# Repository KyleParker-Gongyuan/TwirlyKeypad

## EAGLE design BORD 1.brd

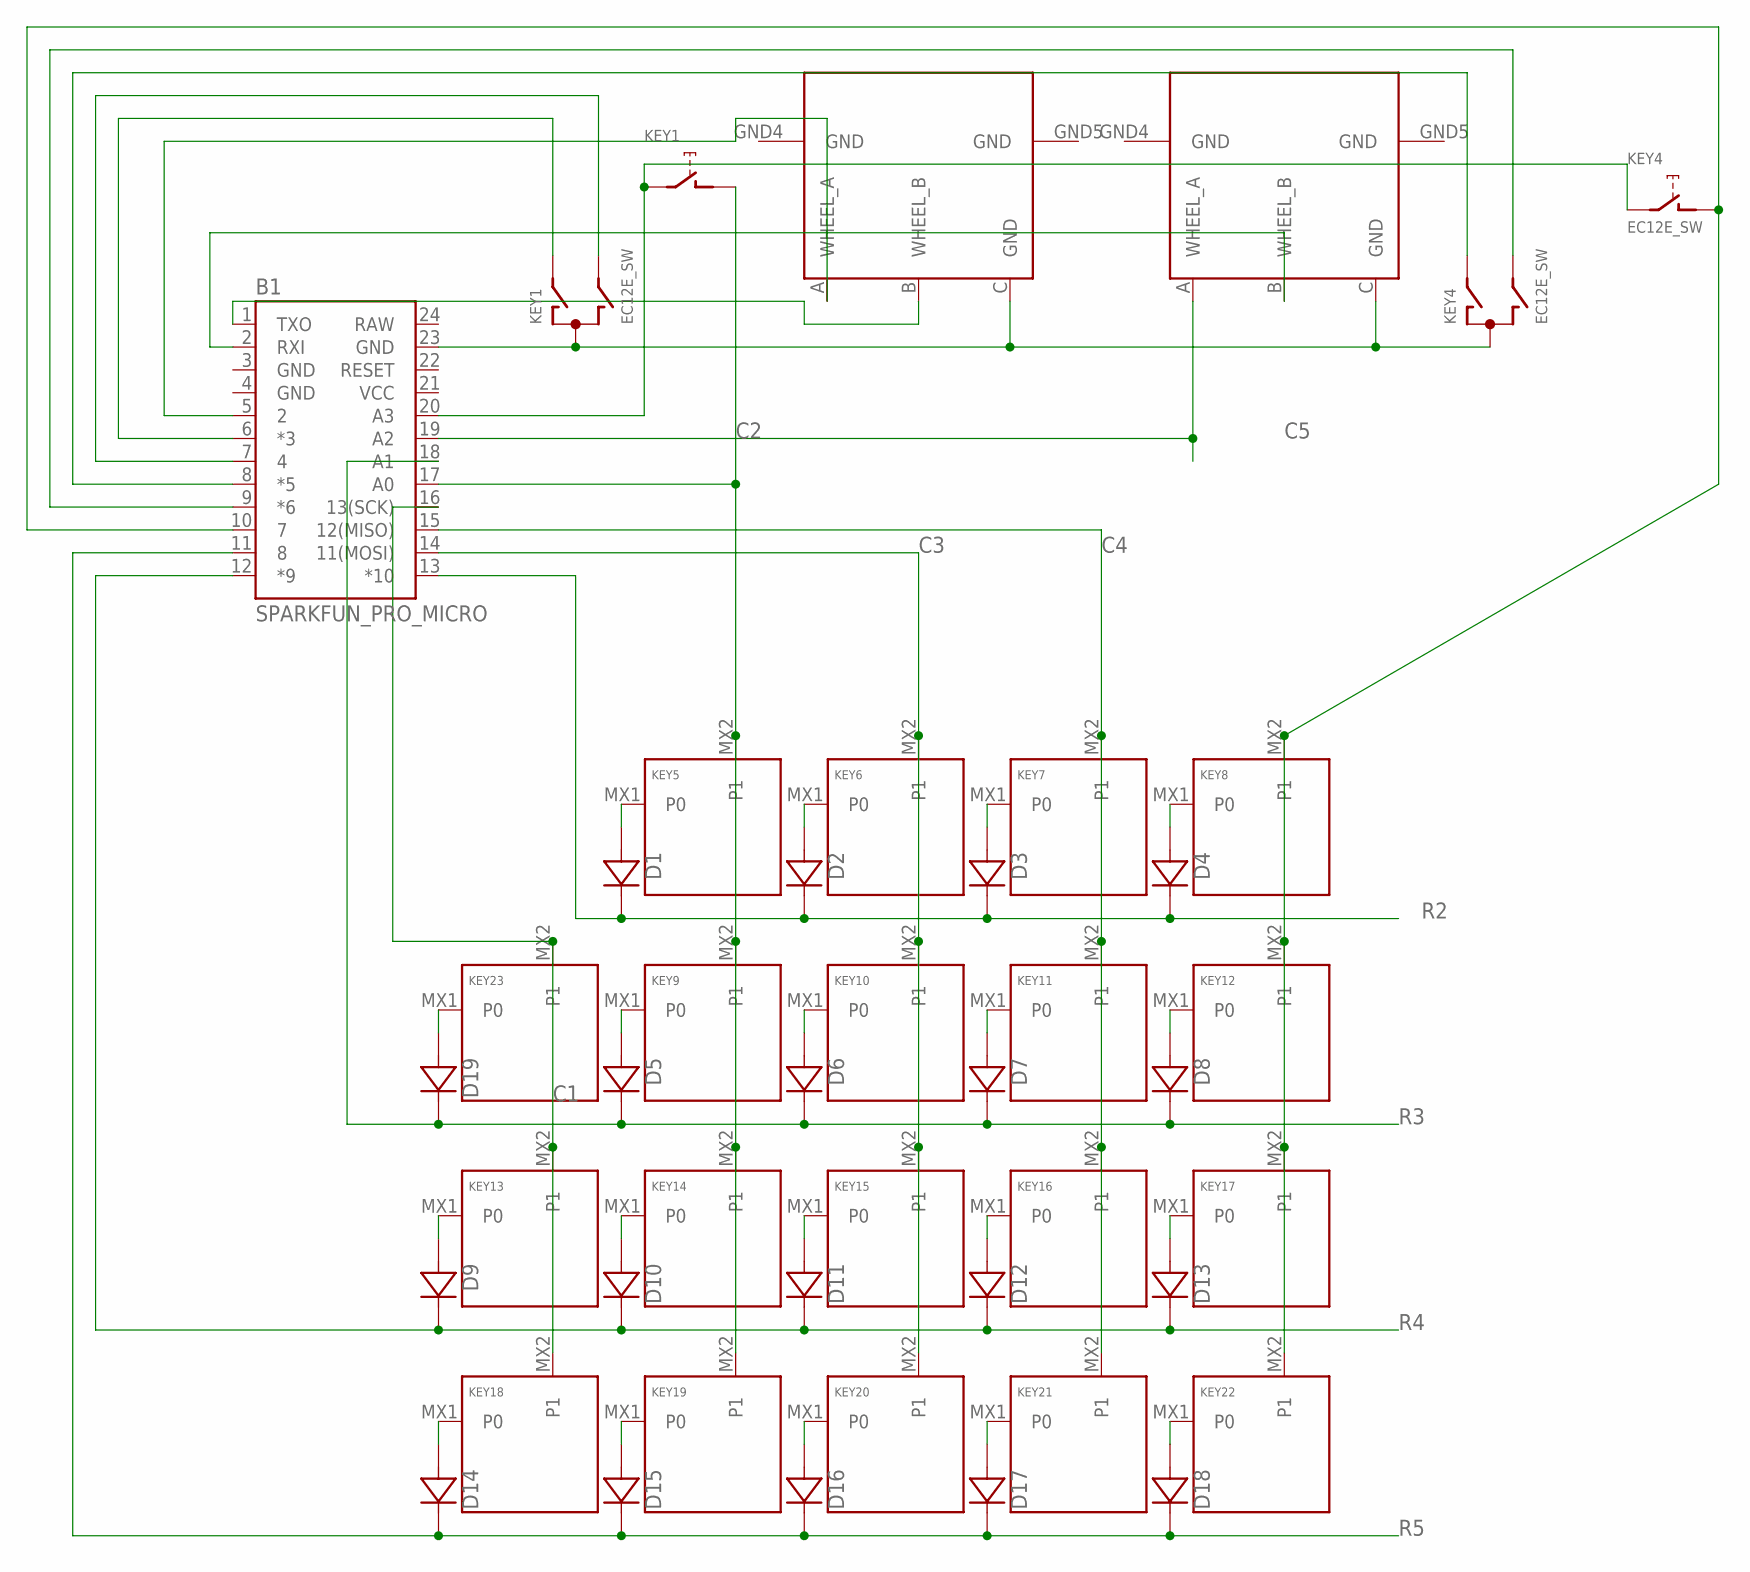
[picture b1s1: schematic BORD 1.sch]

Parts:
B1: SPARKFUN_PRO_MICRO
D1, D2, D3, D4, D5, D6, D7, D8, D9, D10, D11, D12, D13, D14, D15, D16, D17, D18, D19: DIODE-HAND; DIODE_HAND
KEY1, KEY4: EC12E_SW; ALPS_EC12E_SW
KEY2, KEY3: MOUSE_WHEEL_ENCODER; MOUSE-PART
KEY5, KEY6, KEY7, KEY8, KEY9, KEY10, KEY11, KEY12, KEY13, KEY14, KEY15, KEY16, KEY17, KEY18, KEY19, KEY20, KEY21, KEY22, KEY23: KEYSWITCH-PLAIN-MX-1U; MX-1U

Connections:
C1: B1.16 (13(SCK)), KEY13.MX2 (P1), KEY18.MX2 (P1), KEY23.MX2 (P1)
C2: B1.17 (A0), KEY1.D (1), KEY5.MX2 (P1), KEY9.MX2 (P1), KEY14.MX2 (P1), KEY19.MX2 (P1)
C3: B1.14 (11(MOSI)), KEY6.MX2 (P1), KEY10.MX2 (P1), KEY15.MX2 (P1), KEY20.MX2 (P1)
C4: B1.15 (12(MISO)), KEY7.MX2 (P1), KEY11.MX2 (P1), KEY16.MX2 (P1), KEY21.MX2 (P1)
C5: B1.10 (7), KEY4.D (1), KEY8.MX2 (P1), KEY12.MX2 (P1), KEY17.MX2 (P1), KEY22.MX2 (P1)
GND: B1.3 (GND), B1.4 (GND)
unnamed: D1.A1 (A), D1.A2 (A), D1.A3 (A), KEY5.MX1 (P0)
unnamed: D2.A1 (A), D2.A2 (A), D2.A3 (A), KEY6.MX1 (P0)
unnamed: D3.A1 (A), D3.A2 (A), D3.A3 (A), KEY7.MX1 (P0)
unnamed: D4.A1 (A), D4.A2 (A), D4.A3 (A), KEY8.MX1 (P0)
unnamed: D5.A1 (A), D5.A2 (A), D5.A3 (A), KEY9.MX1 (P0)
unnamed: D6.A1 (A), D6.A2 (A), D6.A3 (A), KEY10.MX1 (P0)
unnamed: D7.A1 (A), D7.A2 (A), D7.A3 (A), KEY11.MX1 (P0)
unnamed: D8.A1 (A), D8.A2 (A), D8.A3 (A), KEY12.MX1 (P0)
unnamed: D9.A1 (A), D9.A2 (A), D9.A3 (A), KEY13.MX1 (P0)
unnamed: D10.A1 (A), D10.A2 (A), D10.A3 (A), KEY14.MX1 (P0)
unnamed: D11.A1 (A), D11.A2 (A), D11.A3 (A), KEY15.MX1 (P0)
unnamed: D12.A1 (A), D12.A2 (A), D12.A3 (A), KEY16.MX1 (P0)
unnamed: D13.A1 (A), D13.A2 (A), D13.A3 (A), KEY17.MX1 (P0)
unnamed: D14.A1 (A), D14.A2 (A), D14.A3 (A), KEY18.MX1 (P0)
unnamed: D15.A1 (A), D15.A2 (A), D15.A3 (A), KEY19.MX1 (P0)
unnamed: D16.A1 (A), D16.A2 (A), D16.A3 (A), KEY20.MX1 (P0)
unnamed: D17.A1 (A), D17.A2 (A), D17.A3 (A), KEY21.MX1 (P0)
unnamed: D18.A1 (A), D18.A2 (A), D18.A3 (A), KEY22.MX1 (P0)
unnamed: B1.23 (GND), KEY1.C, KEY2.C (GND), KEY3.C (GND), KEY4.C
unnamed: B1.20 (A3), KEY1.E (2), KEY4.E (2)
unnamed: B1.6 (*3), KEY1.A
unnamed: B1.7 (4), KEY1.B
unnamed: B1.8 (*5), KEY4.A
unnamed: B1.19 (A2), KEY3.A (WHEEL_A)
unnamed: B1.5 (2), KEY2.A (WHEEL_A)
unnamed: B1.1 (TXO), KEY2.B (WHEEL_B)
unnamed: B1.9 (*6), KEY4.B
unnamed: D19.A1 (A), D19.A2 (A), D19.A3 (A), KEY23.MX1 (P0)
unnamed: B1.2 (RXI), KEY3.B (WHEEL_B)
R2: B1.13 (*10), D1.C1 (C), D1.C2 (C), D1.C3 (C), D2.C1 (C), D2.C2 (C), D2.C3 (C), D3.C1 (C), D3.C2 (C), D3.C3 (C), D4.C1 (C), D4.C2 (C), D4.C3 (C)
R3: B1.18 (A1), D5.C1 (C), D5.C2 (C), D5.C3 (C), D6.C1 (C), D6.C2 (C), D6.C3 (C), D7.C1 (C), D7.C2 (C), D7.C3 (C), D8.C1 (C), D8.C2 (C), D8.C3 (C), D19.C1 (C), D19.C2 (C), D19.C3 (C)
R4: B1.12 (*9), D9.C1 (C), D9.C2 (C), D9.C3 (C), D10.C1 (C), D10.C2 (C), D10.C3 (C), D11.C1 (C), D11.C2 (C), D11.C3 (C), D12.C1 (C), D12.C2 (C), D12.C3 (C), D13.C1 (C), D13.C2 (C), D13.C3 (C)
R5: B1.11 (8), D14.C1 (C), D14.C2 (C), D14.C3 (C), D15.C1 (C), D15.C2 (C), D15.C3 (C), D16.C1 (C), D16.C2 (C), D16.C3 (C), D17.C1 (C), D17.C2 (C), D17.C3 (C), D18.C1 (C), D18.C2 (C), D18.C3 (C)
RAW: B1.24 (RAW)
VCC: B1.21 (VCC)

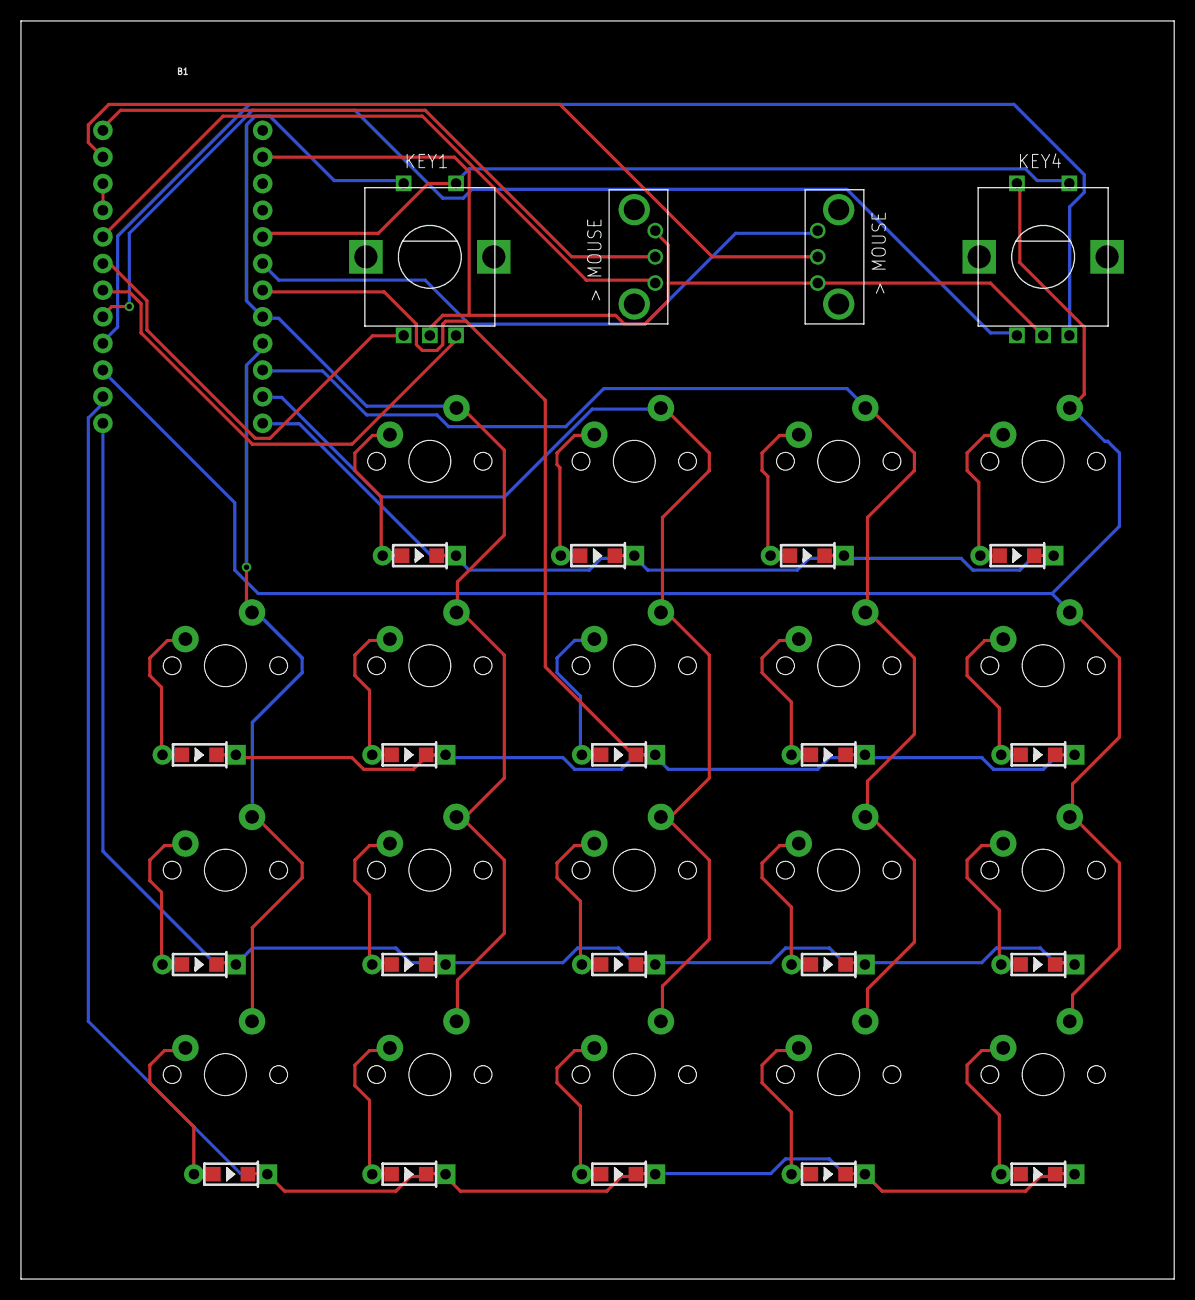
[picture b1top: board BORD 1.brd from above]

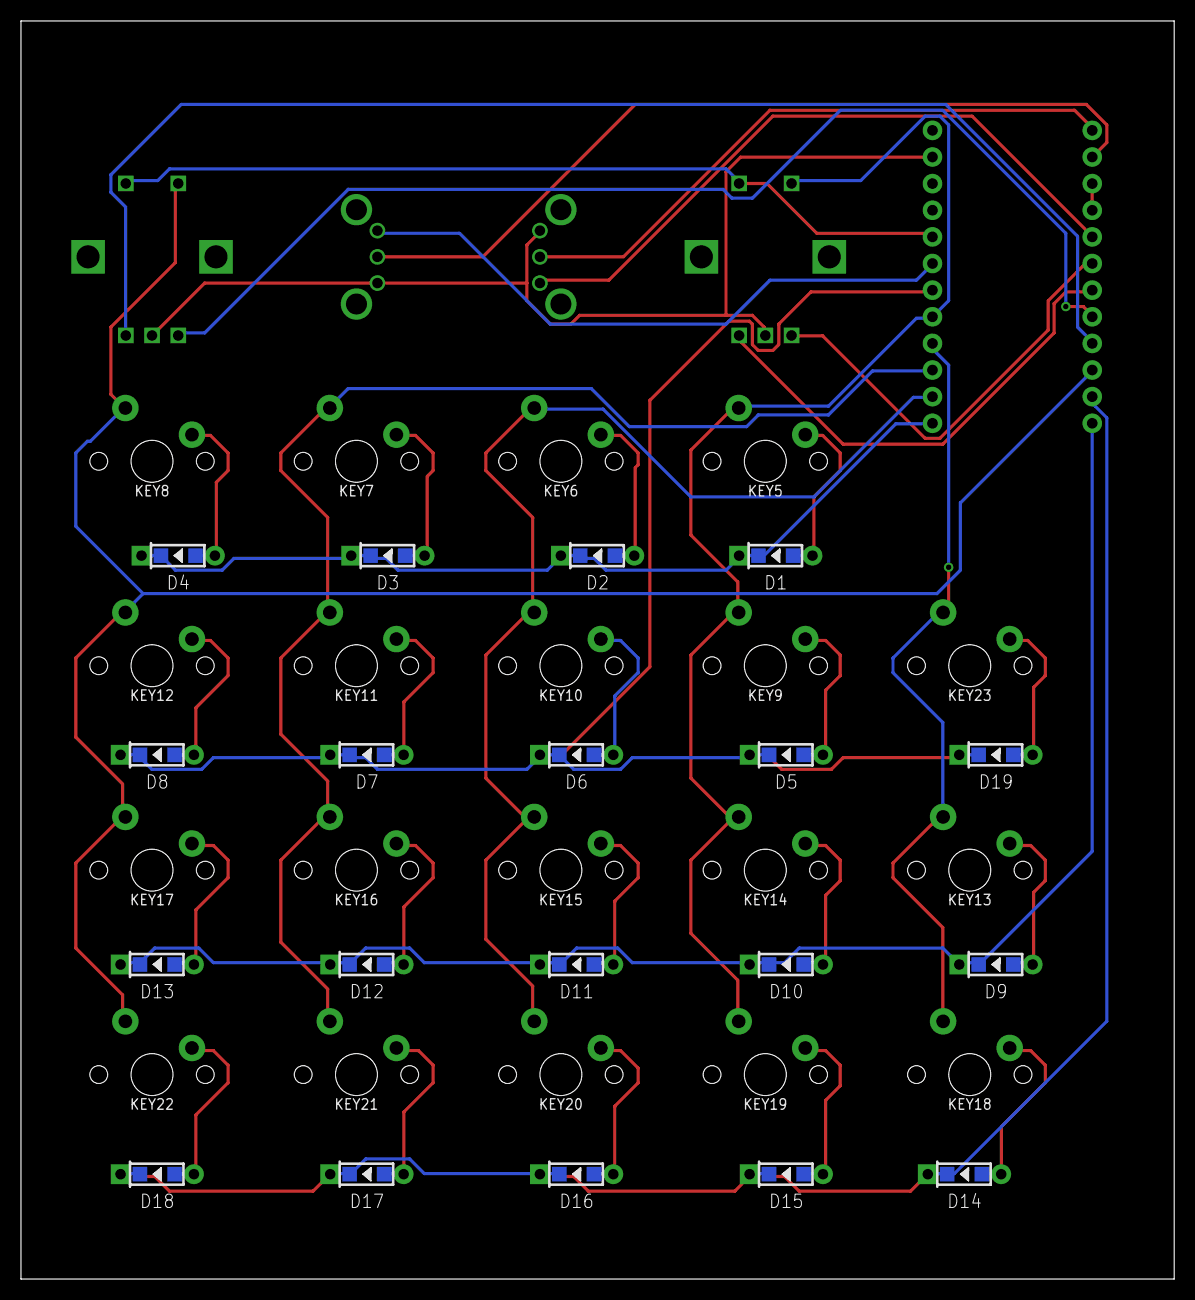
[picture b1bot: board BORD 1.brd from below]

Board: 2 copper layers, 110.0 x 120.0 mm, 43 parts (19 on the bottom side), 39 nets.

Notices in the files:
parts and their libraries:
SparkFun-Boards: Licensing: Creative Commons ShareAlike 4.0 International - https://creativecommons.org/licenses/by-sa/4.0
